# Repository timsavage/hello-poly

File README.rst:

############################################
Hello Poly - Polyphonic MIDI to CV interface
############################################

Polyphonic MIDI to CV module for modular synths, hardware designed for Eurorack systems.

Features:

- 6x 12bit DACs with a range of 0-~8.192V (assignable as either Note or Control outputs)
- 4x Gate outputs
- Configurable CV range 1V/Octave or 1.2V/Octave (providing a 100mV/step)
- Fully assignable routing of MIDI messages by channel
- Assignable Pitchbend and Channel Aftertouch
- Multiple Polyphony modes
- Support for multiple programs (controlled via program change events)
- Configuration via MIDI
- Gate controlled LFO.
- Firmware is hardware agnostic, could be compiled for other targets.

Hardware
========

- Designed around an STM32F411 32bit ARM MCU
- MSP4822 12bit DACs
- 128x64 SSD1306 OLED display

Software
========

Software currently using Arduino, however, I am migrating to using CMSIS and the STM32 HAL 
using the STM32CubeIDE mainly for the debugging support!

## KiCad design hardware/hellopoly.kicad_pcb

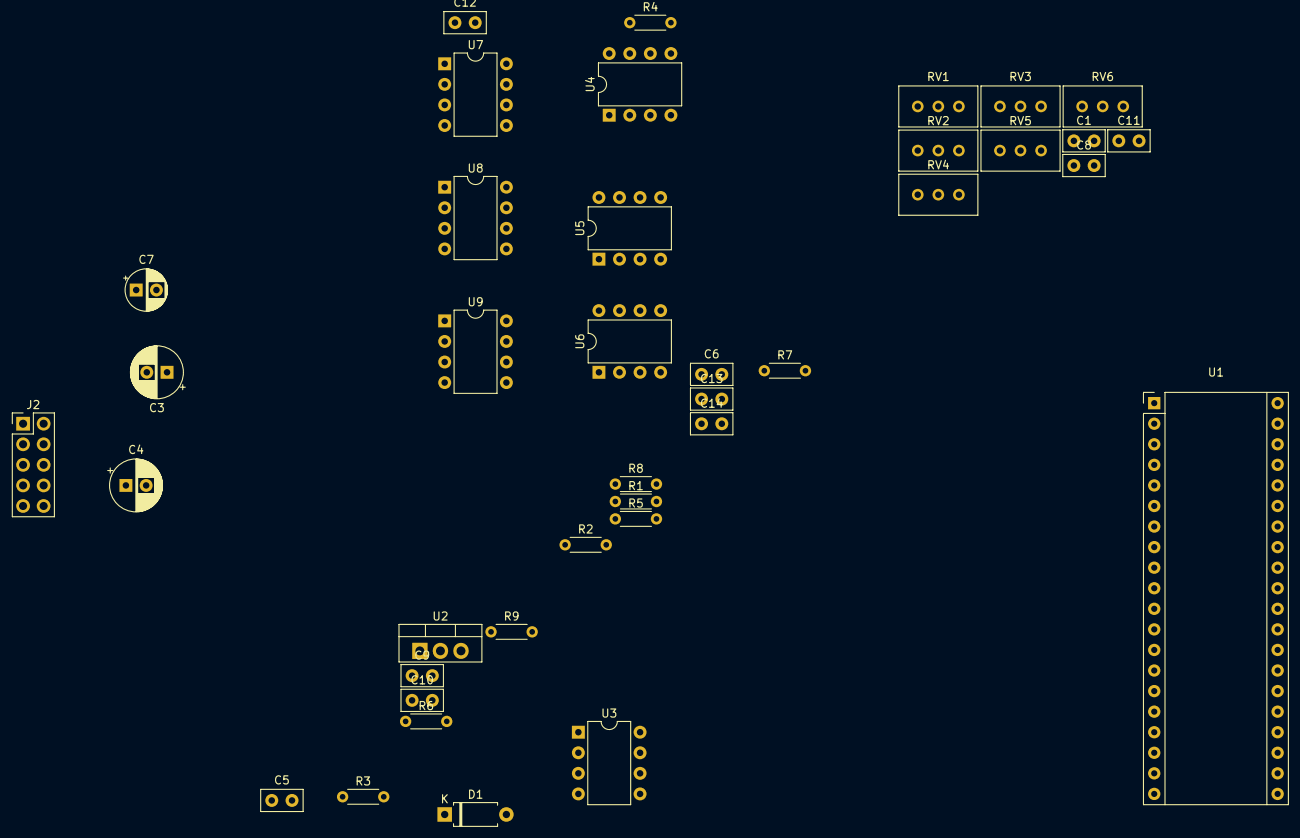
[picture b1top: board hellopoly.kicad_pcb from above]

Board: 2 copper layers, 39 parts (0 on the bottom side), 38 nets, no tracks yet.

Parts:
C1, C5, C6, C8, C9, C10, C11, C12, C13, C14: 0.1uF; C_Disc_D5.0mm_W2.5mm_P2.50mm
C3, C4: 47u; CP_Radial_D6.3mm_P2.50mm
C7: 47uF; CP_Radial_D5.0mm_P2.50mm
D1: 1N4148; D_A-405_P7.62mm_Horizontal
J2: Power BUS; PinHeader_2x05_P2.54mm_Vertical
R1: 220R; R_Axial_DIN0204_L3.6mm_D1.6mm_P5.08mm_Horizontal
R2, R4, R5, R6, R7, R8, R9: 10K; R_Axial_DIN0204_L3.6mm_D1.6mm_P5.08mm_Horizontal
R3: 470K; R_Axial_DIN0204_L3.6mm_D1.6mm_P5.08mm_Horizontal
RV1, RV2, RV3, RV4, RV5, RV6: 10K; Potentiometer_Bourns_3296W_Vertical
U1: Bluepill; Maple_Mini
U2: L7805; TO-220-3_Vertical
U3: 6N138; DIP-8_W7.62mm
U4, U5, U6: TL072; DIP-8_W7.62mm
U7, U8, U9: MCP4822; DIP-8_W7.62mm

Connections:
+5V: C7.1, C8.1, C11.1, C12.1, R3.1, U1.38, U2.3, U3.8, U7.1, U8.1, U9.1
+12V: C1.1, C3.1, C5.1, C9.1, C13.1, U2.1, U4.8, U5.8, U6.8
-12V: C4.2, C6.2, C10.2, C14.2, U4.4, U5.4, U6.4
DAC1_CV: R4.1, U4.7
DAC2_CV: R5.1, U4.1
DAC3_CV: R6.1, U5.7
DAC4_CV: R7.1, U5.1
DAC5_CV: R8.1, U6.7
DAC6_CV: R9.1, U6.1
DACA_CS: U1.7, U7.2
DACB_CS: U1.8, U8.2
DACC_CS: U1.9, U9.2
GND: C1.2, C7.2, C8.2, C11.2, C12.2, J2.4, J2.6, J2.8, RV1.2, RV1.3, RV2.2, RV2.3, RV3.2, RV3.3, RV4.2, RV4.3, RV5.2, RV5.3, RV6.2, RV6.3, U1.19, U1.20, U1.39, U2.2, U7.5, U7.7, U8.5, U8.7, U9.5, U9.7
MIDI_RX: R3.2, U1.16, U3.6
unnamed: C3.2, C4.1, J2.3, J2.5, J2.7
unnamed: C5.2, C6.1
unnamed: C9.2, C10.1
unnamed: C13.2, C14.1
unnamed: D1.1, R1.1, U3.2
unnamed: D1.2, U3.3
unnamed: J2.9, J2.10
unnamed: J2.1, J2.2
unnamed: R2.1, U3.7
unnamed: R2.2, U3.5
unnamed: R4.2, RV1.1, U4.6
unnamed: R5.2, RV2.1, U4.2
unnamed: R6.2, RV3.1, U5.6
unnamed: R7.2, RV4.1, U5.2
unnamed: R8.2, RV5.1, U6.6
unnamed: R9.2, RV6.1, U6.2
unnamed: U4.3, U7.6
unnamed: U4.5, U7.8
unnamed: U5.3, U8.6
unnamed: U5.5, U8.8
unnamed: U6.3, U9.6
unnamed: U6.5, U9.8
SPI1_MOSI: U1.12, U7.4, U8.4, U9.4
SPI1_SCK: U1.10, U7.3, U8.3, U9.3

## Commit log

2019-03-03 Renamed to just devices.hpp, added MIDI port to comment
2019-03-04 Migrated to split header/implementation
2019-03-04 Restructured to move hardware definition away into devices namespace
2019-03-04 Merged hal into devices
2019-03-05 Added some core files and a blank readme
2019-03-05 Moved into firmware folder
2019-03-06 Started laying out the core
2019-03-06 Addded readm
2019-03-06 Initial class spec for Program
2019-03-07 Rough MIDI interface working
2019-03-07 Added base class for the Polyphony model
2019-03-07 Filled out gate implimentation
2019-03-08 Updated note and polyphony setup
2019-03-08 Built out polyphony and setup devices, super basic router.
2019-03-08 Extended midi interface and return supported values
2019-03-08 Tweaks to message handling to handle short messages better
2019-03-08 Added polybuffer
2019-03-08 Started building ordered polyphony mode
2019-03-09 Store the current note on a key
2019-03-09 Simplify Mono model by using key note storage
2019-03-09 Built out Low mode of positional
2019-03-09 Tweaked interface
2019-03-09 Improved routing and listen for more midi events
2019-03-11 Created key list to handle common search operations
2019-03-11 Built out mono modes
2019-03-11 Added Mock dac to simplfy testing
2019-03-11 Updated docs
2019-03-11 Built out Positional model
2019-03-11 Added python simulation of the positional model
2019-03-11 Updates to hardware and description
2019-03-12 Added aftertouch callback
2019-03-12 Split polyphony modes into classes
2019-03-12 Support pitch bend in a key
2019-03-12 Re-ordered main file and handle aftertouch
2019-03-12 Started modeling positional models
2019-03-12 Use control messages to control mode
2019-03-12 Removed tempoary mode definition
2019-03-12 Added basic control class
2019-03-13 Added name
2019-03-13 Merged into hpp
2019-03-13 Added aftertouch event
2019-03-13 Removed polybuffer define
2019-03-13 Enabled display and one DAC
2019-03-15 Added basics or UI
2019-03-21 Ported Adafruit SSD1306, stripped out SPI Made faster for I2C
2019-03-21 Blacked
2019-03-21 Initial View interface
2019-03-21 Migrated to using customised display driver
2019-03-25 Added ignore file
2019-03-25 Normalised all polyphonic interfaces
2019-03-25 Fixed display corruption
2019-03-26 Rebuilt display driver from modified Adafruit library
2019-03-26 Directly use SSD1306 driver
2019-03-26 Testing rendering and scrolling
2019-03-28 Moved route table into router object
2019-03-28 Ignore python version
2019-03-31 Initial KiCad files
2019-03-31 Removed many warnings
2019-03-31 Split router
2019-03-31 Swapped in 128x64 display
2019-03-31 Moved modes into router
2019-03-31 updated to 128x64 pixel display
2019-03-31 Set correct display size
2019-04-01 Started building layout, added footprint for display
